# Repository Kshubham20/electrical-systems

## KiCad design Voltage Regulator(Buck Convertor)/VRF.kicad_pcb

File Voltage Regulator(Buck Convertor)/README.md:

# TPS51397A 5.5-V to 24-V, 10-A Synchronous Buck Converter with ULQ™ Operation
### Design Parameters

- VOUT Output voltage 5 V
- IOUT Output current 10 A
- ΔVOUT Transient response 1-A — 9-A load step, 2.5 A/μs ±5% x VOUT
- VIN Input voltage 5.5 to 24 V
- VOUT(ripple) Output voltage ripple 0-A — 10-A loading 2% x VOUT
- FSW Switching frequency 500 kHz
- Light load operating mode Eco-mode
- TA Ambient temperature 25 °C

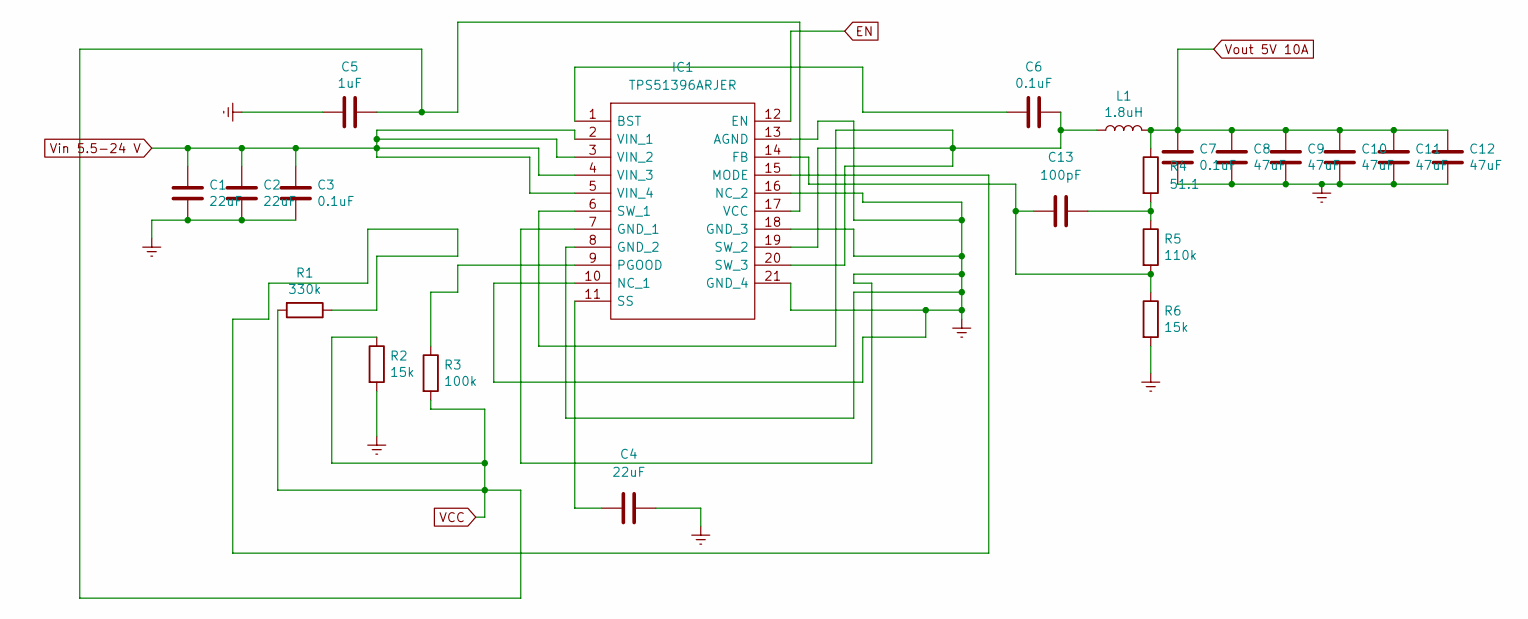
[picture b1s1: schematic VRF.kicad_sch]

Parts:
C1, C2, C4: 22uF; C_0805_2012Metric_Pad1.18x1.45mm_HandSolder
C3, C6, C7: 0.1uF; C_0805_2012Metric_Pad1.18x1.45mm_HandSolder
C5: 1uF; C_0603_1608Metric_Pad1.08x0.95mm_HandSolder
C8, C9, C10, C11, C12: 47uF; C_0805_2012Metric_Pad1.18x1.45mm_HandSolder
C13: 100pF; C_0805_2012Metric_Pad1.18x1.45mm_HandSolder
IC1: TPS51396ARJER; Mouser Part Number 595-TPS51396ARJER
L1: 1.8uH; L_Vishay_IHLP-2525
R1: 330k; C_0603_1608Metric_Pad1.08x0.95mm_HandSolder
R2: 15k; C_0603_1608Metric_Pad1.08x0.95mm_HandSolder
R3: 100k; C_0603_1608Metric_Pad1.08x0.95mm_HandSolder
R4: 51.1; C_0603_1608Metric_Pad1.08x0.95mm_HandSolder
R5: 110k; C_0603_1608Metric_Pad1.08x0.95mm_HandSolder
R6: 15k; C_0805_2012Metric_Pad1.18x1.45mm_HandSolder

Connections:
EN: IC1.12 (EN)
Earth: C1.2, C2.2, C3.2, C4.2, C5.1, C7.2, C8.2, C9.2, C10.2, C11.2, C12.2, IC1.7 (GND_1), IC1.8 (GND_2), IC1.10 (NC_1), IC1.13 (AGND), IC1.16 (NC_2), IC1.18 (GND_3), IC1.21 (GND_4), R2.2, R6.2
unnamed: C4.1, IC1.11 (SS)
unnamed: C6.1, IC1.6 (SW_1), IC1.19 (SW_2), IC1.20 (SW_3), L1.1
unnamed: C6.2, IC1.1 (BST)
unnamed: C13.1, IC1.14 (FB), R5.2, R6.1
unnamed: C13.2, R4.2, R5.1
unnamed: IC1.9 (PGOOD), R3.1
unnamed: IC1.15 (MODE), R1.1
VCC: C5.2, IC1.17 (VCC), R1.2, R2.1, R3.2
Vin 5.5-24 V: C1.1, C2.1, C3.1, IC1.2 (VIN_1), IC1.3 (VIN_2), IC1.4 (VIN_3), IC1.5 (VIN_4)
Vout 5V 10A: C7.1, C8.1, C9.1, C10.1, C11.1, C12.1, L1.2, R4.1

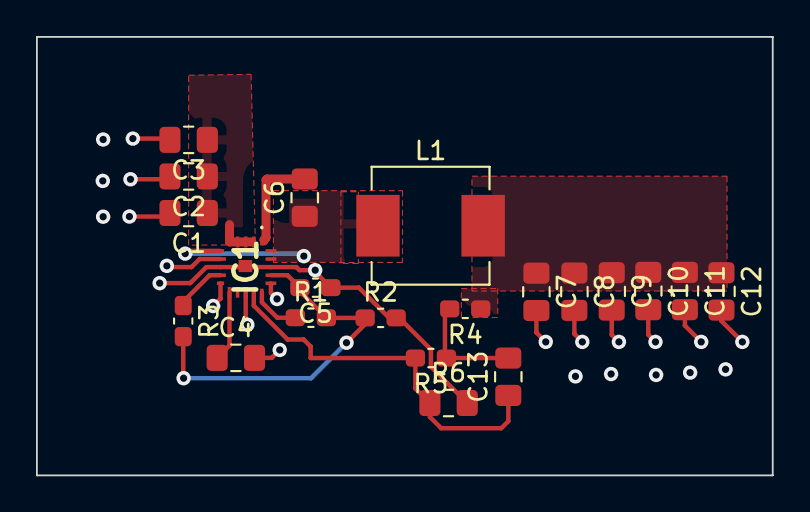
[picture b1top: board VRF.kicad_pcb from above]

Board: 2 copper layers, 40.9 x 24.4 mm, 21 parts (0 on the bottom side), 11 nets.

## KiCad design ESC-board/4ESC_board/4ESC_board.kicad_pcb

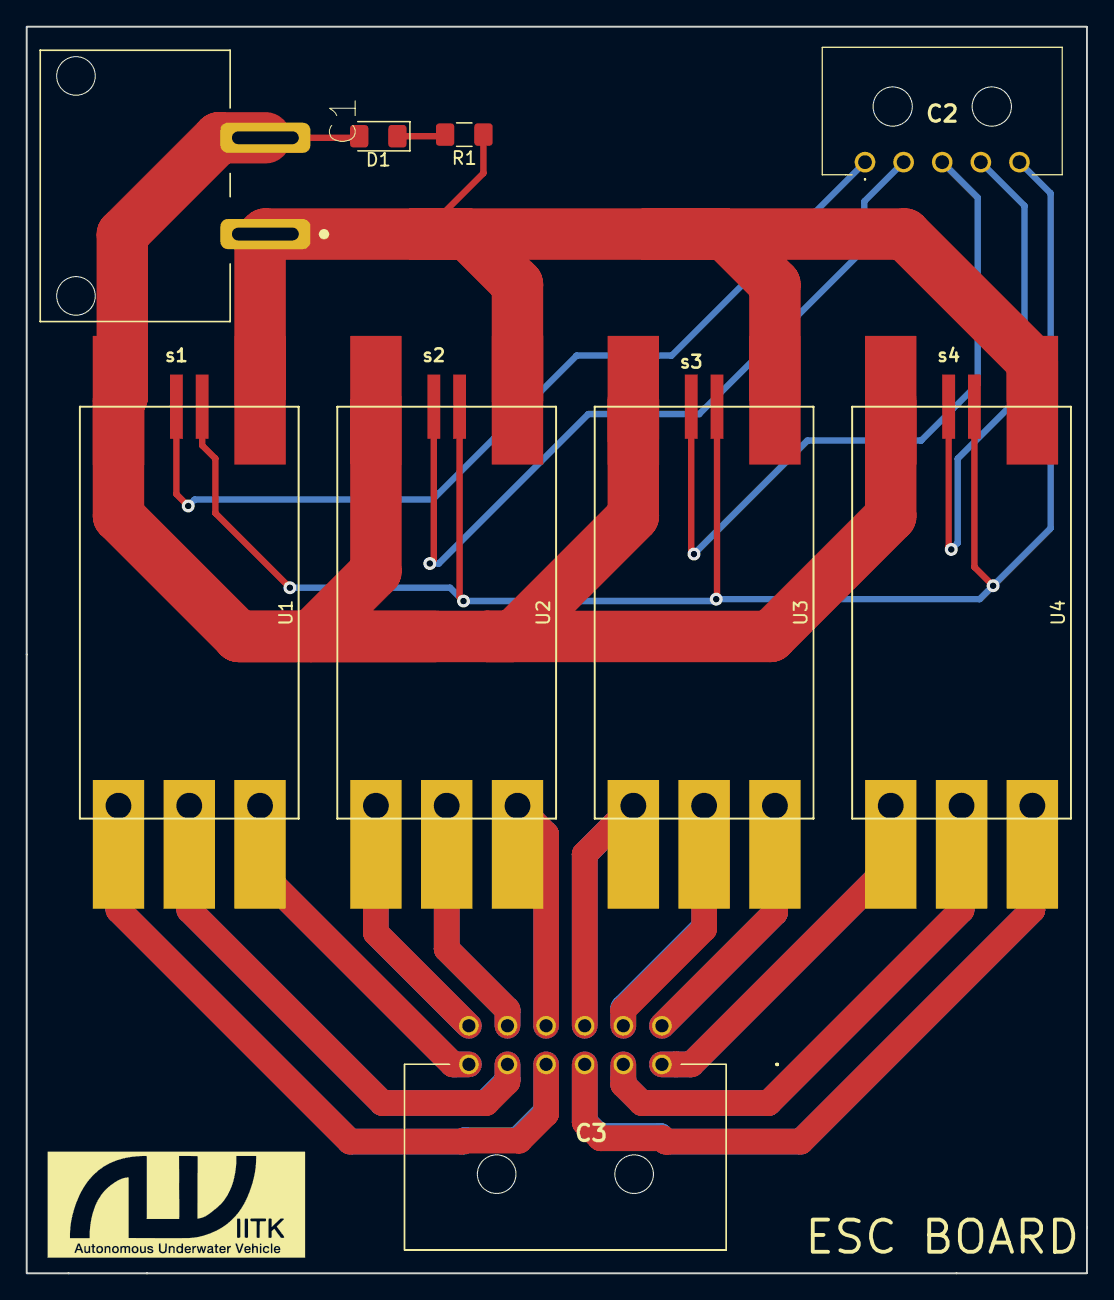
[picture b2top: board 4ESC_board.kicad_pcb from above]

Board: 2 copper layers, 82.4 x 96.9 mm, 9 parts (0 on the bottom side), 20 nets.

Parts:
C1: 1x2_connector; molex_supersabre_1x2_172043-0201
C2: 1x5_connector; Molex_Microfit_1x5_436500500
C3: 6x2_connector; Molex_microfit_2x6_444281201
D1: LED; D_1206_3216Metric_Pad1.42x1.75mm_HandSolder
R1: R; R_1206_3216Metric_Pad1.42x1.75mm_HandSolder
U1, U2, U3, U4: ESCPINS; ESC_footprint

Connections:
/GND: C1.2, R1.1, U1.7, U2.7, U3.7, U4.7
/MGND: C2.5, U1.5, U2.5, U3.5, U4.5
/SPEED1: C2.1, U1.4
/SPEED2: C2.2, U2.4
/SPEED3: C2.3, U3.4
/SPEED4: C2.4, U4.4
/TB1: C3.6, U1.1
/TB2: C3.10, U2.1
/TB3: C3.7, U3.1
/TB4: C3.3, U4.1
/TG1: C3.5, U1.2
/TG2: C3.11, U2.2
/TG3: C3.8, U3.2
/TG4: C3.2, U4.2
/TW1: C3.4, U1.3
/TW2: C3.12, U2.3
/TW3: C3.9, U3.3
/TW4: C3.1, U4.3
/VIN: C1.1, D1.2, U1.6, U2.6, U3.6, U4.6
unnamed: D1.1, R1.2

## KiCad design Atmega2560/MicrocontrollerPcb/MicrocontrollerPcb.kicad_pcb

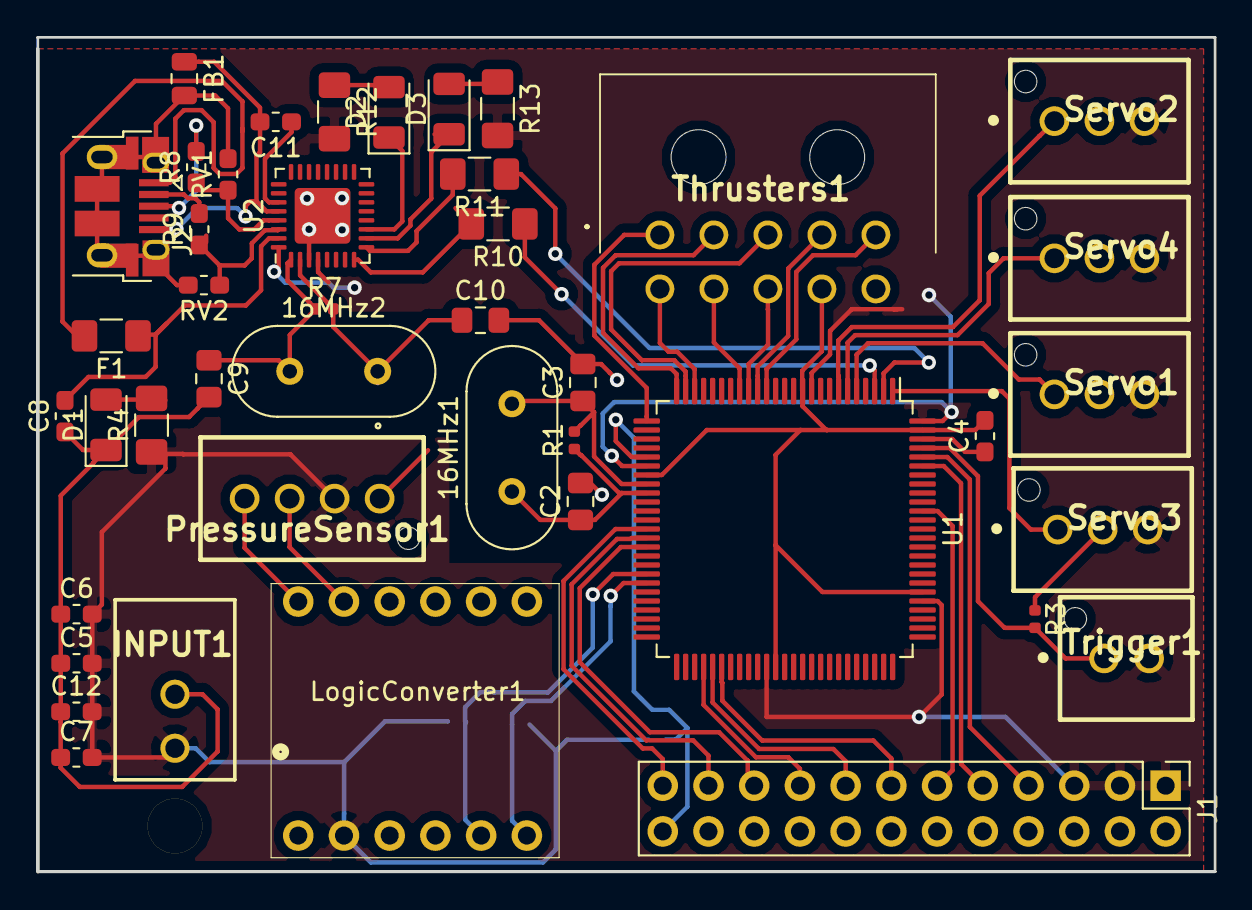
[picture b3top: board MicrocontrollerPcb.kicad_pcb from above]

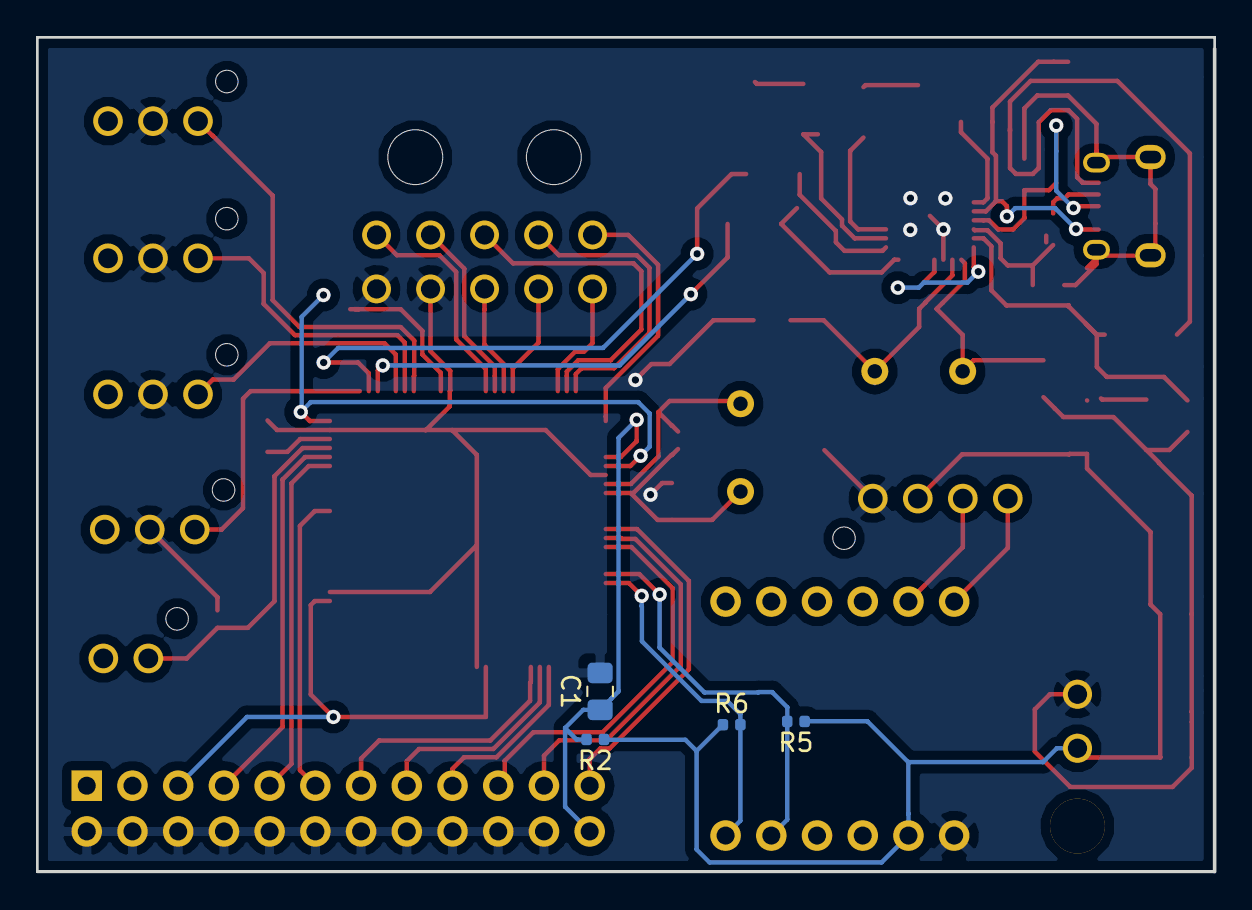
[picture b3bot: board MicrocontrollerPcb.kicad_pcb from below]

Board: 2 copper layers, 65.4 x 46.3 mm, 47 parts (4 on the bottom side), 52 nets.

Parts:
16MHz1, 16MHz2: Crystal; Crystal_HC49-U_Vertical
C1, C2, C3, C9, C10: 22pF; C_0805_2012Metric_Pad1.15x1.40mm_HandSolder
C4, C5, C6, C7, C8, C11, C12: 100n; C_0603_1608Metric_Pad1.05x0.95mm_HandSolder
D1, D2, D3: LED; LED_1206_3216Metric
F1: 500mA; Fuse_1206_3216Metric_Pad1.42x1.75mm_HandSolder
FB1: Ferrite_Bead; R_0805_2012Metric
INPUT1: Conn_01x02_Male; input
J1: Conn_02x12_Odd_Even; PinHeader_2x12_P2.54mm_Vertical
J2: USB_B_Micro; USB_Micro-B_Amphenol_10103594-0001LF_Horizontal
LogicConverter1: Conn_02x06_Counter_Clockwise; 02x06
PressureSensor1: Conn_01x04_Male; 53375-0410
R1, R7: 1M; R_0402_1005Metric
R2: 10k; R_0402_1005Metric
R3, R5, R6: 10K; R_0402_1005Metric
R4, R10, R11, R12, R13: 1K; R_1206_3216Metric_Pad1.42x1.75mm_HandSolder
R8, R9: 22R; R_0603_1608Metric_Pad1.05x0.95mm_HandSolder
RV1, RV2: Varistor; R_0603_1608Metric_Pad1.05x0.95mm_HandSolder
Servo1, Servo2, Servo3, Servo4: Conn_01x03_Male; 01x03
Thrusters1: Connector 02x05; 02x05
Trigger1: Conn_01x02_Female; 53375-0210
U1: ATmega2560-16AU; TQFP-100_14x14mm_P0.5mm
U2: ATmega8U2-MU; QFN-32-1EP_5x5mm_P0.5mm_EP3.1x3.1mm

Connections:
+5V: C5.2, C6.2, C7.2, C12.2, INPUT1.1, J1.1, J1.3, J1.5, LogicConverter1.5, PressureSensor1.2, R2.1, R4.1, R5.1, R6.1, R12.2, R13.2, Servo1.3, Servo2.3, Servo3.3, Servo4.3, Trigger1.2, U1.10, U1.31, U1.61, U1.80, U1.100, U2.4, U2.32
/A1: J1.7, U1.96
/A2: J1.9, U1.95
/A3: J1.11, U1.90
/D1: J1.17, U1.54
/D2: J1.15, U1.55
/D3: J1.13, U1.56
/D+: R8.1, RV1.1, U2.29
/D-: R9.1, RV2.1, U2.30
/PWM1: J1.23, U1.38
/PWM2: J1.21, U1.39
/PWM3: J1.19, U1.40
/RX0: R11.1, U1.2
/Reset: C1.1, J1.24, R2.2, U1.30
/S2: Servo1.1, U1.5
/S3: Servo4.1, U1.6
/S4: Servo2.1, U1.7
/SCL: LogicConverter1.2, R5.2, U1.43
/SDA: LogicConverter1.1, R6.2, U1.44
/T1: Thrusters1.1, U1.26
/T2: Thrusters1.2, U1.25
/T3: Thrusters1.3, U1.24
/T4: Thrusters1.4, U1.16
/T5: Thrusters1.5, U1.15
/T6: Thrusters1.6, U1.23
/T7: Thrusters1.7, U1.18
/T8: Thrusters1.8, U1.17
/TX0: R10.1, U1.3
/USBVCC: C8.2, F1.1, U2.31
Earth: C1.2, C2.2, C3.2, C4.2, C5.1, C6.1, C7.1, C8.1, C9.2, C10.2, C12.1, D1.1, INPUT1.2, J1.2, J1.4, J1.6, J1.8, J1.10, J1.12, J1.14, J1.16, J1.18, J1.20, J1.22, LogicConverter1.6, PressureSensor1.1, R3.1, Servo1.2, Servo2.2, Servo3.2, Servo4.2, Thrusters1.9, Thrusters1.10, U1.11, U1.32, U1.62, U1.81, U1.99, U2.3, U2.33
unnamed: 16MHz1.1, C2.1, R1.1, U1.34
unnamed: 16MHz1.2, C3.1, R1.2, U1.33
unnamed: 16MHz2.1, C9.1, R7.1, U2.1
unnamed: 16MHz2.2, C10.1, R7.2, U2.2
unnamed: C4.1, U1.98
unnamed: C11.1, U2.27
unnamed: C11.2, FB1.1, J2.5, U2.28
unnamed: D1.2, R4.2
unnamed: D2.1, U2.11
unnamed: D2.2, R12.1
unnamed: D3.1, U2.10
unnamed: D3.2, R13.1
unnamed: F1.2, J2.1
unnamed: FB1.2, J2.6, RV1.2, RV2.2
unnamed: J2.2, R9.2
unnamed: J2.3, R8.2
unnamed: LogicConverter1.11, PressureSensor1.3
unnamed: LogicConverter1.12, PressureSensor1.4
unnamed: R3.2, Trigger1.1, U1.97
unnamed: R10.2, U2.8
unnamed: R11.2, U2.9
unnamed: Servo3.1, U1.1

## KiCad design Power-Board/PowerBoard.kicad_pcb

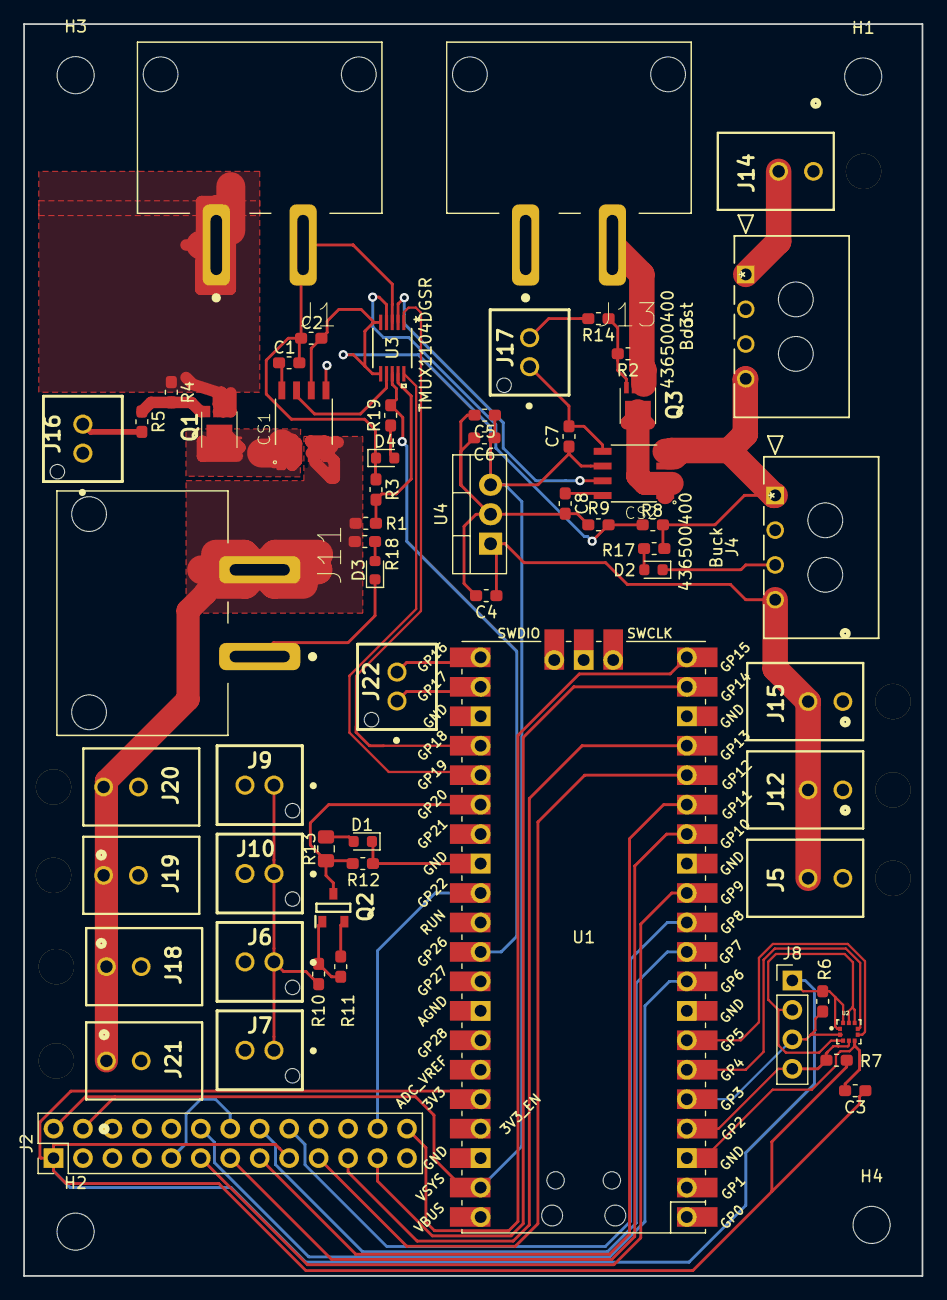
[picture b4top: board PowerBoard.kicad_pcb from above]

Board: 2 copper layers, 77.5 x 107.9 mm, 64 parts (0 on the bottom side), 49 nets.

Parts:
C1, C8: 1nF; C_0603_1608Metric_Pad1.05x0.95mm_HandSolder
C2, C7: 0.1uF; C_0603_1608Metric_Pad1.05x0.95mm_HandSolder
C3: 100n; C_0603_1608Metric_Pad1.05x0.95mm_HandSolder
C4, C5: 10u; C_0603_1608Metric_Pad1.05x0.95mm_HandSolder
C6: 0.1u; C_0603_1608Metric_Pad1.05x0.95mm_HandSolder
CS1, CS2: ACS712ELCTR-30A-T; SOIC127P600X175-8N
D1, D2, D3, D4: LED; LED_0603_1608Metric
H1, H2, H3, H4: MountingHole; MountingHole_3.2mm_M3
J1: IN1; molex_supersabre_1x2_172043-0201
J2: Conn_02x13_Odd_Even; PinHeader_2x13_P2.54mm_Vertical
J3: Boost; CON_436500400_MOL
J4: Buck; CON_436500400_MOL
J5, J12, J15: Buck_out; input
J6: probe1; 01x02
J7: probe4; 01x02
J8: bmp388; PinHeader_1x04_P2.54mm_Vertical
J9: probe2; 01x02
J10: probe3; 01x02
J11: Battery_out; molex_supersabre_1x2_172043-0201
J13: IN2; molex_supersabre_1x2_172043-0201
J14: Boost_out; input
J16, J17, J22: Conn_01x02_Male; 01x02
J18, J19, J20, J21: Battery_out; input
Q1, Q3: SIS427EDN-T1-GE3; SIS862DNT1GE3
Q2: MMBT3906; SOT95P240X120-3N
R1, R8: 2k; R_0603_1608Metric_Pad1.05x0.95mm_HandSolder
R2, R3, R4, R9: 10k; R_0603_1608Metric_Pad1.05x0.95mm_HandSolder
R5, R14: 20k; R_0603_1608Metric_Pad1.05x0.95mm_HandSolder
R6, R7: 4.7k; R_0603_1608Metric_Pad1.05x0.95mm_HandSolder
R10, R12: 1k; R_0603_1608Metric_Pad1.05x0.95mm_HandSolder
R11: 27k; R_0603_1608Metric_Pad1.05x0.95mm_HandSolder
R13: 240; R_0805_2012Metric_Pad1.15x1.40mm_HandSolder
R17, R18, R19: .5k; R_0603_1608Metric_Pad1.05x0.95mm_HandSolder
U1: Pico; RPi_Pico_SMD_TH
U2: BMP388; PQFN50P200X200X80-10N
U3: TMUX1104DGSR; DGS10_TEX
U4: LM7805_TO220; TO-220-3_Vertical

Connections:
/3.3V: C3.1, J2.1, J2.17, J8.1, R6.2, R7.2, U1.36, U2.1, U2.10
/5V: C2.1, C5.1, C6.1, C7.1, CS1.6, CS2.6, J2.2, J2.4, U1.39, U3.5, U3.6, U4.3
/B1B: CS2.3, CS2.4, J3.4, J4.1, R8.1, R17.2
/BOOST_OUT: J3.1, J14.2
/Buck_Out: C4.1, J4.4, J5.2, J12.2, J15.2, U4.1
/CSB: U1.7, U2.6
/CTRL1: U1.24, U3.1
/CTRL2: U1.25, U3.10
/INT: U1.6, U2.7
/K1: J2.12, U1.9
/K2: J2.16, U1.10
/K3: J2.18, U1.11
/LCD_CS: J2.24, U1.29
/MIN1: CS1.7, U3.7
/MIN2: CS2.7, U3.2
/MIN3: R1.2, R3.2, U3.9
/MIN4: R8.2, R9.2, U3.4
/MOS1: CS1.1, CS1.2, Q1.5, Q1.6, Q1.7, Q1.8, Q1.9, Q1.10, Q1.11
/MOS2: CS2.1, CS2.2, Q3.5, Q3.6, Q3.7, Q3.8, Q3.9, Q3.10, Q3.11
/MOUT: R19.2, U1.31, U3.8
/P: J6.1, J7.1, J9.1, J10.1, R10.1
/RS: J2.15, U1.15
/RST: J2.13, U1.14
/RV1: CS1.3, CS1.4, J11.1, J18.1, J19.1, J20.1, J21.1, R1.1, R18.2
/RX: J22.1, U1.22
/SCK: J2.23, U1.19
/SCL: J8.3, R6.1, U1.5, U2.2
/SDA: J8.4, R7.1, U1.4, U2.4
/SI: J2.19, U1.16
/TP_CS: J2.26, U1.20
/TP_IRQ: J2.11, U1.12
/TP_SO: J2.21, U1.17
/TX: J22.2, U1.21
/leak_signal: Q2.3, R12.1, R13.1, U1.26
GND: C1.2, C2.2, C3.2, C4.2, C5.2, C6.2, C7.2, C8.2, CS1.5, CS2.5, D1.1, D2.1, D3.1, D4.1, J1.1, J2.6, J2.9, J2.14, J2.20, J2.25, J3.2, J3.3, J4.2, J4.3, J5.1, J6.2, J7.2, J8.2, J9.2, J10.2, J11.2, J12.1, J13.2, J14.1, J15.1, J16.1, J17.1, J18.2, J19.2, J20.2, J21.2, R3.1, R9.1, R12.2, U1.3, U1.8, U1.13, U1.18, U1.23, U1.28, U1.33, U1.38, U1.42, U2.3, U2.5, U2.8, U2.9, U3.3, U4.2
unnamed: C1.1, CS1.8
unnamed: C8.1, CS2.8
unnamed: D1.2, R13.2
unnamed: D2.2, R17.1
unnamed: D3.2, R18.1
unnamed: D4.2, R19.1
unnamed: J1.2, Q1.1, Q1.2, Q1.3, R4.1
unnamed: J13.1, Q3.1, Q3.2, Q3.3, R2.1
unnamed: J16.2, R5.2
unnamed: J17.2, R14.2
unnamed: Q1.4, R4.2, R5.1
unnamed: Q2.1, R10.2, R11.1
unnamed: Q2.2, R11.2
unnamed: Q3.4, R2.2, R14.1

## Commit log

2021-06-22 Resolved minor issue
2022-12-18 Added Gerber Files

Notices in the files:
parts and their libraries:
Copyright 2016 Accelerated Designs. All rights reserved.
